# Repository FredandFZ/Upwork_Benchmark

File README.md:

# Upwork_Benchmark

ReqMemBench 数据标注、Requirement State Graph 回放、LLM target-time 选择与 Gold State
生成代码仓库。整体流程见 [`Code/README.md`](Code/README.md)，Stage 2 的完整设计和参数说明见
[`Code/README_stage2_gold_state.md`](Code/README_stage2_gold_state.md)。

## Stage 2 Gold State 命令速查

在仓库根目录使用 PowerShell：

```powershell
$py = 'D:\Python_env\Miniconda\python.exe'
$projectId = '42204309'
```

只准备 Candidate Packets，不调用 LLM：

```powershell
& $py Code\stage2_generate_gold_state.py --project-id $projectId --prepare-only
```

只完成 LLM evaluation、生成 threshold 5–10 统计表，不生成最终 Gold：

```powershell
& $py Code\stage2_generate_gold_state.py --project-id $projectId
```

使用已有 evaluation 离线重建并打印 threshold 表，不调用 LLM：

```powershell
& $py Code\stage2_generate_gold_state.py --project-id $projectId --threshold-report-only
```

按指定 threshold 信任 AI、跳过人工审核并直接生成 Gold：

```powershell
& $py Code\stage2_generate_gold_state.py `
  --project-id $projectId `
  --auto-accept-ai `
  --score-threshold 7
```

人工审核模式：

```powershell
Copy-Item `
  "outputs\stage2\$projectId\target_time_human_review.template.json" `
  "outputs\stage2\$projectId\target_time_human_review.json"

& $py Code\stage2_generate_gold_state.py `
  --project-id $projectId `
  --finalize `
  --human-review-file "outputs\stage2\$projectId\target_time_human_review.json"
```

强制重新调用 LLM 评估全部 Candidate：

```powershell
& $py Code\stage2_generate_gold_state.py --project-id $projectId --force-evaluation
```

更多模型、并发、输入路径、resume 和输出参数见
[`Code/README_stage2_gold_state.md` 的“完整命令速查”](Code/README_stage2_gold_state.md#完整命令速查)。

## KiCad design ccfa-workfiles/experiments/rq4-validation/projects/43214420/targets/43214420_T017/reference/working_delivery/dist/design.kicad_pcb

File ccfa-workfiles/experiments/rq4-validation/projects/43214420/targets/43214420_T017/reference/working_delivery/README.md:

# 43214420

Deterministic KiCad-compatible schematic and PCB generator with structural checks for the currently active hardware design state.

## Commands

- `python scripts/build.py`
- `python scripts/check.py`
- `python -m unittest discover -s tests`
- `python src/cli.py list`
- `python scripts/serve.py`

## Structured artifact contract

Edit `src/artifact_model.py`, build the repository, then inspect the generated structure with `python scripts/inspect_artifacts.py`.

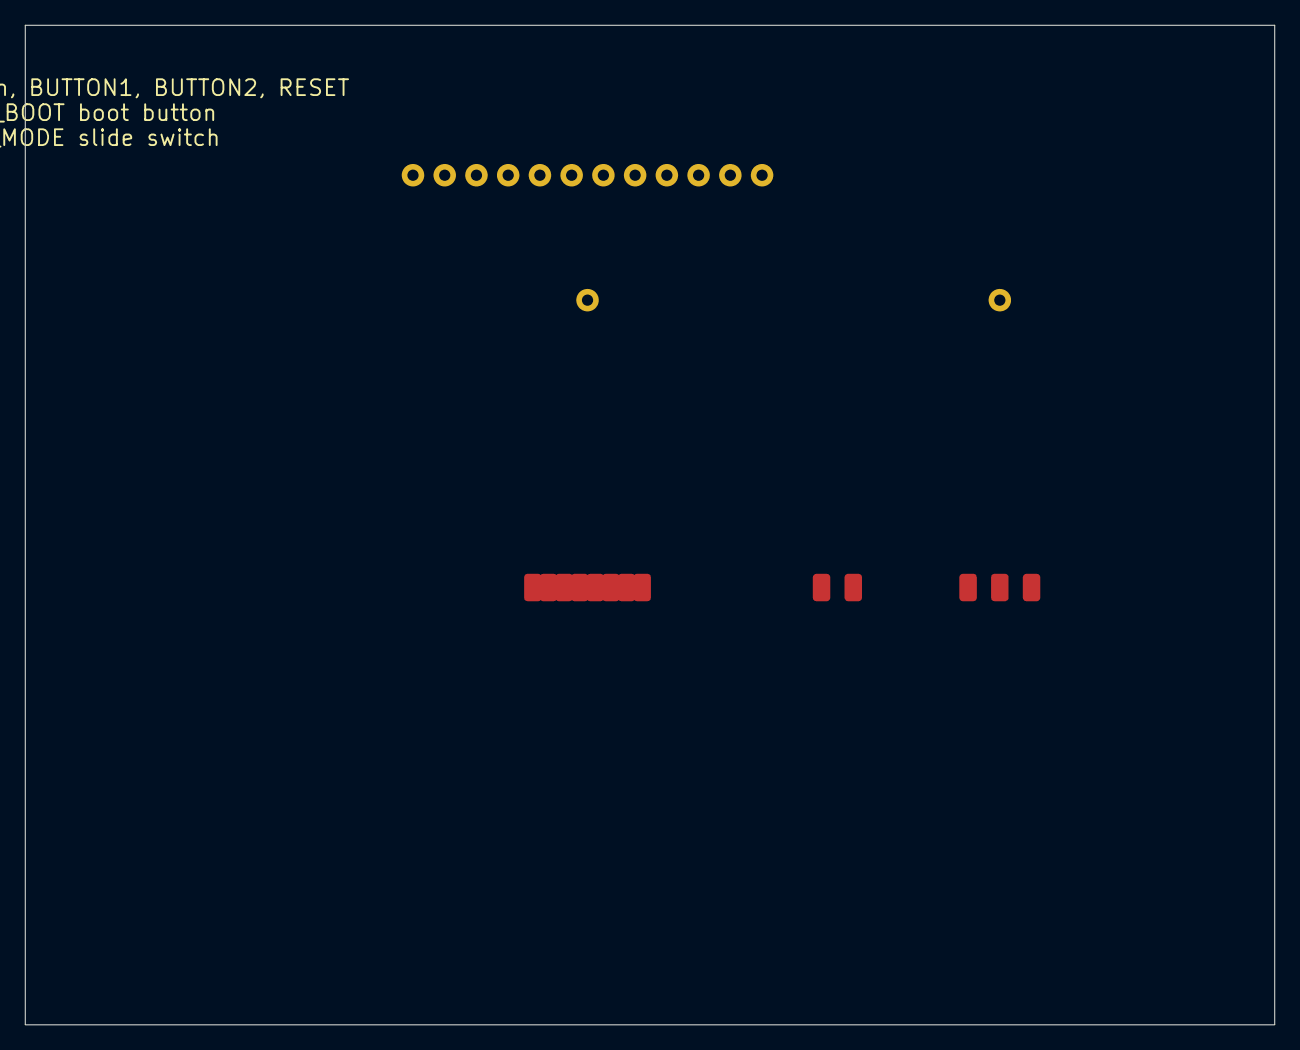
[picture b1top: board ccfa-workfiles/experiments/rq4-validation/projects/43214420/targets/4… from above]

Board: 2 copper layers, 100.0 x 80.0 mm, 28 parts (0 on the bottom side), 2 nets, no tracks yet.

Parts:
C1: Main-Board Local Decoupling; C_0603
D1: Addressable LED Board Array; LED_SMD
D2: Main-Board Power Source OR-ing; LED_SMD
D3: Main-Board Addressable-LED Power and Logic; LED_SMD
J1: Board Identification and Pin Markings; Connector_Generic
J2: Interboard Power and Signal Links; JST-PH_2.0mm_4-pin
J3: Main-Board Connector Inventory; Connector_Generic
J4: Main-Board Panel Controls and Inputs; Connector_Generic
J5: Power-Board Battery Interface; Connector_Generic
J6: Battery-Charge Status Output; Connector_Generic
J7: Power-Board Mechanical Layout; Connector_Generic
J8: Power-Board USB-C Connector; Connector_Generic
J_PANEL: Panel touch/buttons/reset connector; JST_GH_BM08B-GHS-TBT_1x08-1MP_P1.25mm_Horizontal
R1: I2C Bus Electrical Configuration; R_0603
R2: Main-Board I2C Signal Conditioning; R_0603
SW1: Switched 5V Boost Supply; Package_Generic
SW_BOOT: Boot push button; SW_SPST_TL3301AN
SW_MODE: Panel mode slide switch; SW_SPDT_CK_JS102011SAQN
U1: Component Sourceability; Package_Generic
U2: Main-Board ESP32 GPIO Assignments; Package_Generic
U3: Main-Board Rail Current Monitoring; Package_Generic
U4: Main-Board Standalone USB Power; Package_Generic
U5: Power-Board AXP2101 Topology; Package_Generic
U6: Power-Board Battery Protection; Package_Generic
U7: Power-Board Battery Temperature Monitoring; Package_Generic
U8: Power-Board Layer Stack; Package_Generic
U9: Power-Board Production Package; Package_Generic
U10: Power-Board TVS ESD Protection; Package_Generic

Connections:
3V3: J2.1, J_PANEL.7
GND: J2.2, J_PANEL.6, J_PANEL.8, SW_BOOT.2, SW_MODE.2

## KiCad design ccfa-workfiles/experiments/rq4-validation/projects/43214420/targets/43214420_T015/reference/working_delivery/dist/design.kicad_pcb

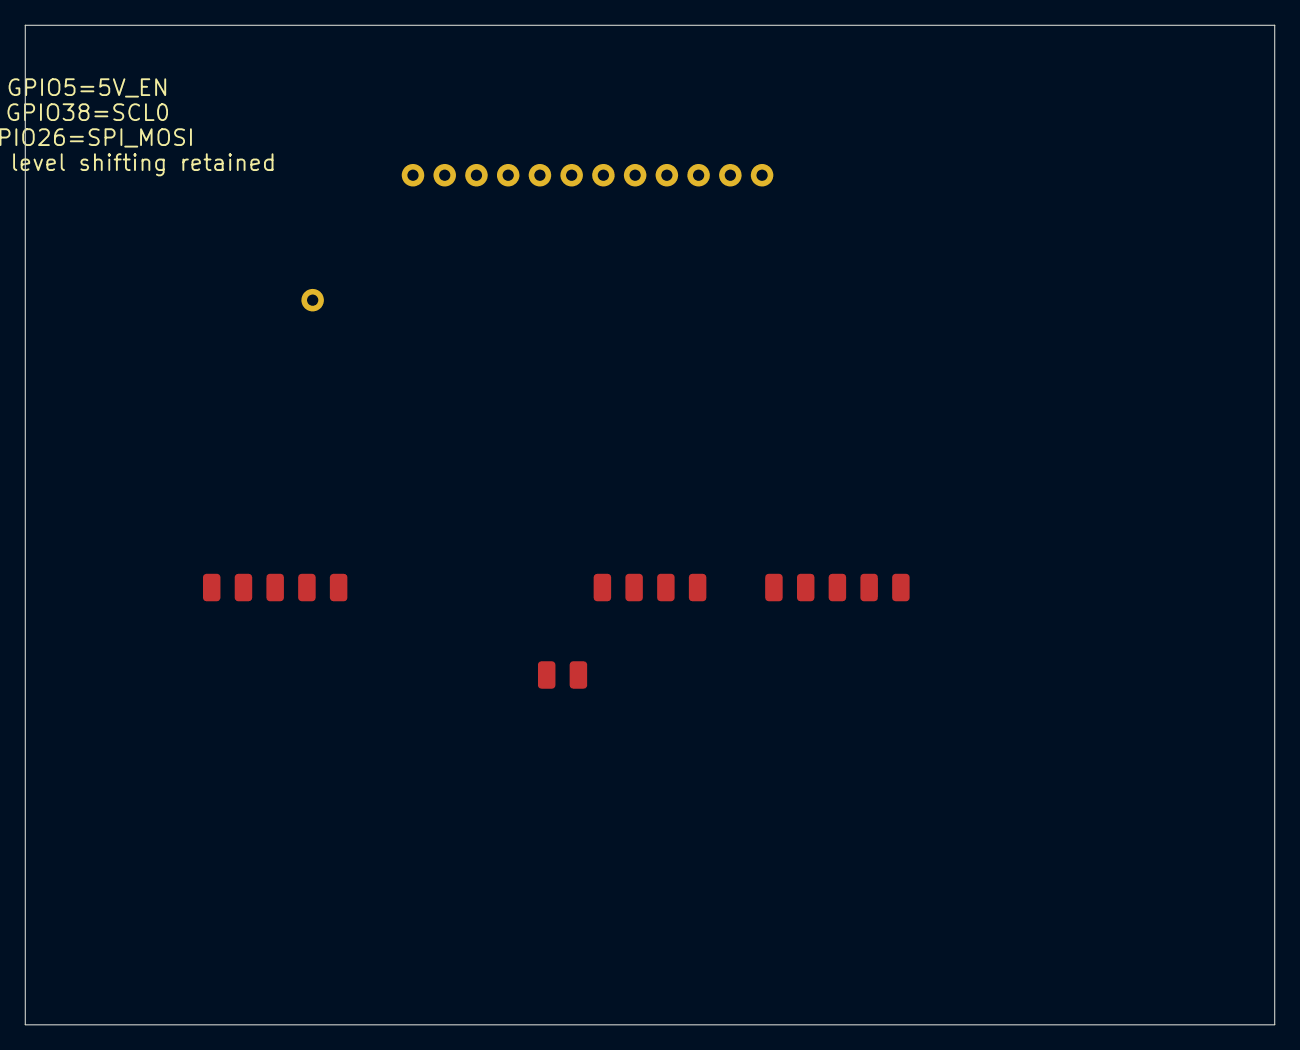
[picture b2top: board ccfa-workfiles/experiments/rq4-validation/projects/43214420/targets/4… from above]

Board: 2 copper layers, 100.0 x 80.0 mm, 24 parts (0 on the bottom side), 5 nets, no tracks yet.

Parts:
D1: Addressable LED Board Array; LED_SMD
D2: Main-Board Power Source OR-ing; LED_SMD
D3: Main-Board Addressable-LED Power and Logic; LED_SMD
J1: Board Identification and Pin Markings; Connector_Generic
J2: Interboard Power and Signal Links; JST-PH_2.0mm_4-pin
J3: Power-Board Battery Interface; Connector_Generic
J4: Battery-Charge Status Output; Connector_Generic
J5: Power-Board Mechanical Layout; Connector_Generic
J6: Power-Board USB-C Connector; Connector_Generic
R1: I2C Bus Electrical Configuration; R_0603
R_EN: 330kΩ; R_0603_1608Metric
SW1: Switched 5V Boost Supply; Package_Generic
U1: Component Sourceability; Package_Generic
U2: Main-Board ESP32 GPIO Assignments; Package_Generic
U3: Main-Board Standalone USB Power; Package_Generic
U4: Power-Board AXP2101 Topology; Package_Generic
U5: Power-Board Battery Protection; Package_Generic
U6: Power-Board Battery Temperature Monitoring; Package_Generic
U7: Power-Board Layer Stack; Package_Generic
U8: Power-Board Production Package; Package_Generic
U9: Power-Board TVS ESD Protection; Package_Generic
U_BOOST: 5V boost 1200mA; WQFN-20-1EP_3x4mm_P0.4mm_EP1.65x2.65mm
U_LS: 74AHCT1G125 level shifter; SOT-23-5
U_MCU: ESP32-S3 controller; ESP32-S3-WROOM-1

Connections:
5V_EN: J2.11, R_EN.1, U_BOOST.2, U_MCU.5
GND: J2.2, R_EN.2, U_BOOST.4, U_LS.1, U_LS.3, U_MCU.G
LED_5V: U_BOOST.3, U_LS.5
LED_DATA_3V3: U_LS.2, U_MCU.13
SCL0: J2.6, U_MCU.38

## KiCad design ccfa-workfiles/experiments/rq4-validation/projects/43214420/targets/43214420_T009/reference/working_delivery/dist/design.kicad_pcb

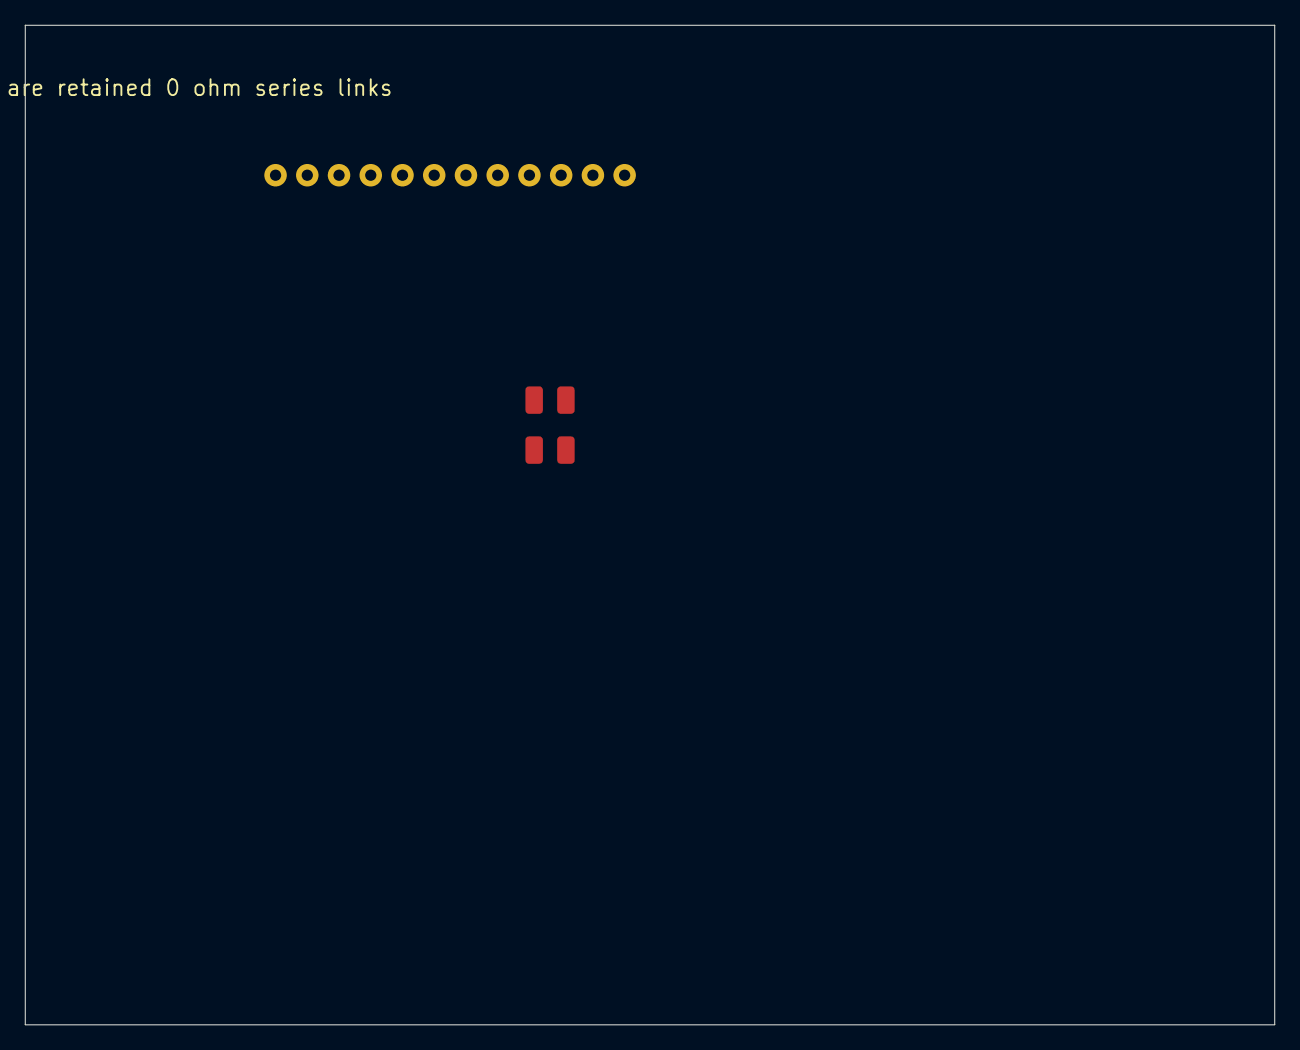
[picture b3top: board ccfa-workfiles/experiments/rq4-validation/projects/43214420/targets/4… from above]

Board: 2 copper layers, 100.0 x 80.0 mm, 14 parts (0 on the bottom side), 2 nets, no tracks yet.

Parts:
D1: Battery-Charge Status Output; LED_SMD
J1: Interboard Power and Signal Links; JST-PH_2.0mm_4-pin
J2: Power-Board Battery Interface; Connector_Generic
J3: Power-Board Mechanical Layout; Connector_Generic
J4: Power-Board USB-C Connector; Connector_Generic
R_SCL: 0Ω; R_0603_1608Metric
R_SDA: 0Ω; R_0603_1608Metric
SW1: Switched 5V Boost Supply; Package_Generic
U1: Component Sourceability; Package_Generic
U2: I2C Bus Electrical Configuration; Package_Generic
U3: Power-Board Battery Protection; Package_Generic
U4: Power-Board Battery Temperature Monitoring; Package_Generic
U5: Power-Board Layer Stack; Package_Generic
U6: Power-Board TVS ESD Protection; Package_Generic

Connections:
SCL0: J1.6, R_SCL.2
SDA0: J1.5, R_SDA.2
